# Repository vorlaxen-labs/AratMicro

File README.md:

# AratMicro

High-performance, open-source **micromouse** robot platform built for **[Robosam](https://robosam.org/)** and **MEB Robot** (Ministry of National Education Robotics Competition, Turkey).

AratMicro is a competition-focused maze-solving robot with a custom PCB, wall-detection sensors, dual-encoder drive, and STM32F411-based firmware. Hardware and software are developed together; all design files are shared in this repository.

## Competition target

This robot is designed to meet the maze-solving requirements of:

- **Robosam** — national robotics competition (micromouse / labyrinth category)
- **MEB Robot** — Ministry of National Education (MEB) robotics competition for schools

The mechanical dimensions, sensor layout, and control architecture are tuned for fast, reliable maze exploration and shortest-path solving under competition rules.

## Features

| Area | Detail |
|------|--------|
| **MCU** | STM32F411CEU6 — Cortex-M4 @ 100 MHz, 512 KB Flash, 128 KB RAM |
| **Motor driver** | DRV8833 — dual-channel H-bridge |
| **Wall sensors** | 4× IR receivers + 4× IR LEDs (front left/right, left, right) |
| **Maze solver** | Flood fill (16×16 grid) |
| **Position feedback** | Left/right quadrature encoders (L_ENC_A/B, R_ENC_A/B) |
| **I/O expansion** | PCF8574AP — I2C GPIO expander |
| **Power** | 2S LiPo → AP63203WU buck (3.3 V logic), separate motor rail |
| **Programming** | ST-Link SWD (PA13/PA14), optional UART Bluetooth |
| **Firmware** | PlatformIO + Arduino framework, C++17 |

## Mechanical (target parts)

| Part | Size | Notes |
|------|------|-------|
| **Motor** | 40 × 12 × 17 mm | 3 mm D-shaft |
| **Wheel** | 32 × 7 mm | 3 mm D-shaft |

> Mechanical CAD files are not yet included. Dimensions were chosen to match the PCB and drivetrain layout.

## Repository layout

```
AratMicro/
├── hardware/
│   └── pcb/          # KiCad 10 schematics and PCB (AratMicro.kicad_pro)
├── software/
│   ├── src/          # Firmware source code
│   ├── include/      # Public API headers
│   ├── lib/          # PlatformIO module libraries
│   ├── test/         # Host-side unit tests (Unity)
│   ├── docs/         # Architecture and hardware reference
│   └── platformio.ini
├── LICENSE
└── CONTRIBUTING.md
```

## Quick start

### Requirements

- [PlatformIO](https://platformio.org/) (VS Code extension or CLI)
- ST-Link V2 (or compatible programmer)
- KiCad 10.x (for hardware edits)

### Build and upload firmware

```bash
cd software
pio run -e aratmicro_f411
pio run -e aratmicro_f411 -t upload
```

### Host tests

Algorithms and core logic can be tested on the host:

```bash
cd software
pio test -e native
```

### Hardware

KiCad project: `hardware/pcb/AratMicro.kicad_pro`

Schematic sub-sheets:

| Sheet | File | Contents |
|-------|------|----------|
| Power Supply | `power_supply.kicad_sch` | 2S LiPo input, buck, protection |
| MCU | `mcu.kicad_sch` | STM32F411, clocks, SWD, I/O |
| Motor Controller | `mc.kicad_sch` | DRV8833 motor driver |
| Sensor Unit | `su.kicad_sch` | IR wall-detection circuit |

Full BOM and signal list: [`hardware/README.md`](hardware/README.md)

## Software architecture

Firmware is organized in layers:

- **core** — Hardware-independent application lifecycle
- **platform** — Time and pin abstractions
- **lib/** — Motor, IMU, maze solver modules (planned)

Details: [`software/docs/architecture.md`](software/docs/architecture.md)

## Status

| Component | Status |
|-----------|--------|
| PCB schematic | Active development |
| PCB layout | Active development |
| Firmware skeleton | Available |
| Motor driver code | Planned |
| Wall sensor code | Planned |
| Maze solver (flood fill) | Available (host-tested) |
| Mechanical CAD | Planned |

## Contributing

Contributions are welcome. Please read [`CONTRIBUTING.md`](CONTRIBUTING.md).

## License

This project is released under the [MIT License](LICENSE) — hardware and software may be used, modified, and shared freely.

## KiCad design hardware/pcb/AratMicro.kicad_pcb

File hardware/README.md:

# AratMicro — Hardware

KiCad 10 main board (PCB) design for the Robosam and MEB Robot micromouse platform. Project file: [`pcb/AratMicro.kicad_pro`](pcb/AratMicro.kicad_pro)

## Schematic hierarchy

```
AratMicro.kicad_sch
├── Power Supply/      power_supply.kicad_sch
├── MCU/               mcu.kicad_sch
├── Motor Controller Unit/   mc.kicad_sch
└── Sensor Unit/       su.kicad_sch
```

## Key components (BOM summary)

| Ref | Part | Description |
|-----|------|-------------|
| U2 | STM32F411CEU6 | Main MCU, UFQFPN-48 |
| U3 | DRV8833PWP | Dual H-bridge motor driver, HTSSOP-16 |
| U4 | PCF8574AP | I2C GPIO expander |
| U1 | AP63203WU | 2 A buck, fixed 3.3 V output |
| Y1 | 8 MHz crystal | HSE |
| Y2 | 32.768 kHz crystal | LSE (RTC) |
| BZ1 | Murata PKMCS0909E | Piezo buzzer |
| J (LiPo) | 2S LiPo connector | Battery input |

Protection: polyfuse, TVS diode, AO3401A P-channel MOSFET (power path).

## MCU signal map

Signal names are taken from schematic hierarchical labels. STM32 pin assignments will be finalized during PCB layout.

### Motor driver (DRV8833)

| Signal | Direction | Description |
|--------|-----------|-------------|
| MC_IN1 | MCU → DRV | Motor A direction 1 |
| MC_IN2 | MCU → DRV | Motor A direction 2 |
| MC_BIN1 | MCU → DRV | Motor B direction 1 |
| MC_BIN2 | MCU → DRV | Motor B direction 2 |
| MC_SLEEP | MCU → DRV | Sleep / enable |
| MC_FAULT | DRV → MCU | Fault output |
| AOUT1, AOUT2 | DRV → motor | Motor A |
| BOUT1, BOUT2 | DRV → motor | Motor B |

### Encoders

| Signal | Description |
|--------|-------------|
| L_ENC_A, L_ENC_B | Left wheel quadrature |
| R_ENC_A, R_ENC_B | Right wheel quadrature |

### Wall sensors (IR)

| Signal | Description |
|--------|-------------|
| IR_ON | Enable IR LEDs (Sensor Unit) |
| REC_F_L | Front-left receiver |
| REC_F_R | Front-right receiver |
| REC_L | Left wall receiver |
| REC_R | Right wall receiver |

The Sensor Unit uses 4× IR receivers paired with 4× IR LEDs (one emitter per direction: front-left, front-right, left, right). LED drivers are controlled via BC817 NPN transistors.

### Other

| Signal | Description |
|--------|-------------|
| SNIFF_SDA, SNIFF_SCL | I2C (IMU / external sensor bus) |
| BT_TX, BT_RX | UART — wireless module (optional) |
| Buzzer | Audio feedback |
| LED1–LED4 | Status LEDs |
| PA13, PA14 | SWD (ST-Link) |
| NRST, BOOT0 | Reset and boot mode |
| BATTS | Battery voltage (ADC) |

## Power architecture

```
2S LiPo (7.4 V nominal)
    │
    ├── Motor rail ──► DRV8833 VM
    │
    └── AP63203WU buck ──► +3.3 V logic
            │
            ├── STM32F411
            ├── PCF8574AP
            └── Sensor Unit (IR circuit)
```

Logic runs at 3.3 V; motor supply is driven directly from the battery rail. Polyfuse and TVS provide input protection.

## Mechanical interface

The drivetrain is designed for these off-the-shelf parts:

| Part | Size |
|------|------|
| DC motor | 40 × 12 × 17 mm, 3 mm D-shaft |
| Wheel | 32 × 7 mm, 3 mm D-shaft |

Motor connectors are defined on the Motor Controller Unit sheet.

## Opening in KiCad

1. Install KiCad 10.x.
2. Open `pcb/AratMicro.kicad_pro`.
3. Use the top-level hierarchy sheet in Eeschema to navigate sub-sheets.

## Fabrication

When PCB layout is complete:

- Export Gerber and drill files to `hardware/pcb/fabrication/`.
- BOM CSV: Eeschema → Tools → Generate Bill of Materials.

> **Note:** Layout and fabrication files are not final yet; the repository version is under active development.

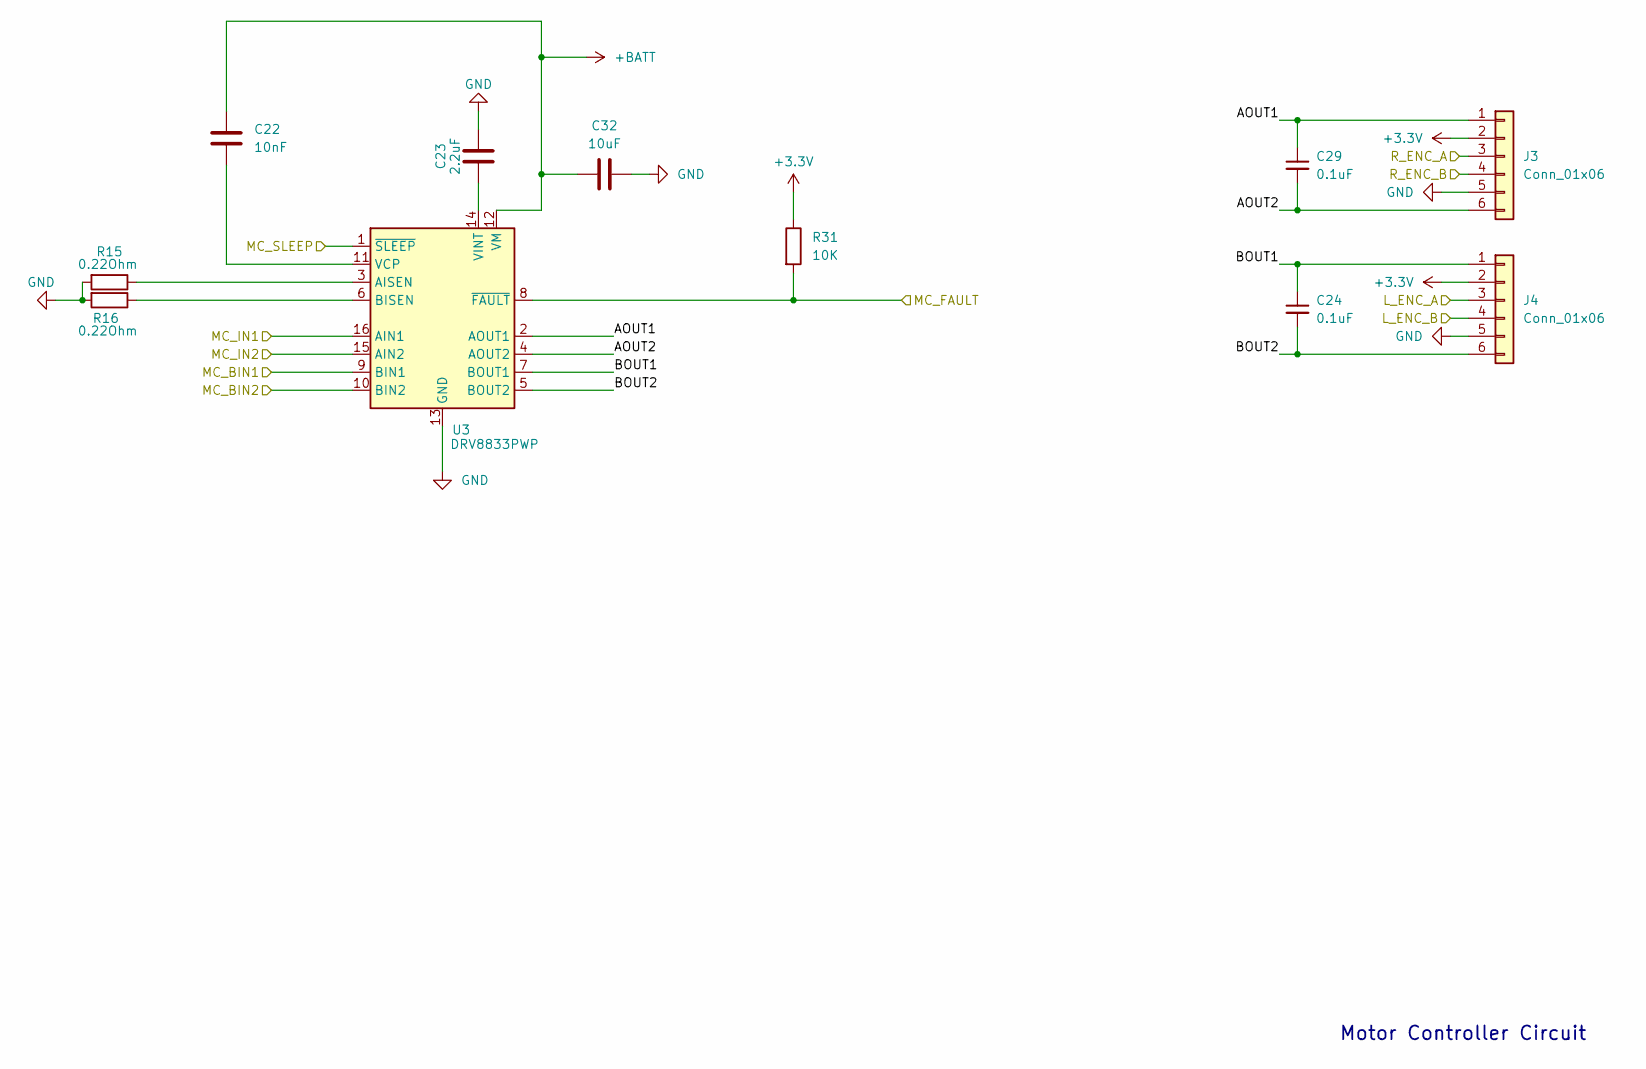
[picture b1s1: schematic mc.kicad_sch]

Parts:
C22: 10nF; C_0603_1608Metric
C23: 2.2uF; C_0603_1608Metric
C24, C29: 0.1uF; C_0603_1608Metric
C32: 10uF; C_0805_2012Metric
J3, J4: Conn_01x06; PinHeader_1x06_P2.54mm_Vertical
R15, R16: 0.22Ohm; R_0805_2012Metric
R31: 10K; R_0603_1608Metric
U3: DRV8833PWP; HTSSOP-16-1EP_4.4x5mm_P0.65mm_EP3.4x5mm_Mask2.46x2.31mm_The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

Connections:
+3.3V: J3.2, J4.2, R31.1; also elsewhere on the board
+BATT: C22.1, C32.1, U3.12 (VM); also elsewhere on the board
/Microcontroller Unit/L_ENC_A: J4.3; also elsewhere on the board
/Microcontroller Unit/L_ENC_B: J4.4; also elsewhere on the board
/Microcontroller Unit/MC_BIN1: U3.9 (BIN1); also elsewhere on the board
/Microcontroller Unit/MC_BIN2: U3.10 (BIN2); also elsewhere on the board
/Microcontroller Unit/MC_FAULT: R31.2, U3.8 (~FAULT); also elsewhere on the board
/Microcontroller Unit/MC_IN1: U3.16 (AIN1); also elsewhere on the board
/Microcontroller Unit/MC_IN2: U3.15 (AIN2); also elsewhere on the board
/Microcontroller Unit/MC_SLEEP: U3.1 (~SLEEP); also elsewhere on the board
/Microcontroller Unit/R_ENC_A: J3.3; also elsewhere on the board
/Microcontroller Unit/R_ENC_B: J3.4; also elsewhere on the board
/Motor Controller/AOUT1: C29.1, J3.1, U3.2 (AOUT1)
/Motor Controller/AOUT2: C29.2, J3.6, U3.4 (AOUT2)
/Motor Controller/BOUT1: C24.1, J4.1, U3.7 (BOUT1)
/Motor Controller/BOUT2: C24.2, J4.6, U3.5 (BOUT2)
GND: C23.2, C32.2, J3.5, J4.5, R15.2, R16.2, U3.13 (GND), U3.17 (GND); also elsewhere on the board
unnamed: R15.1, U3.3 (AISEN)
unnamed: R16.1, U3.6 (BISEN)
unnamed: C22.2, U3.11 (VCP)
unnamed: C23.1, U3.14 (VINT)

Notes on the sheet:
Motor Controller Circuit

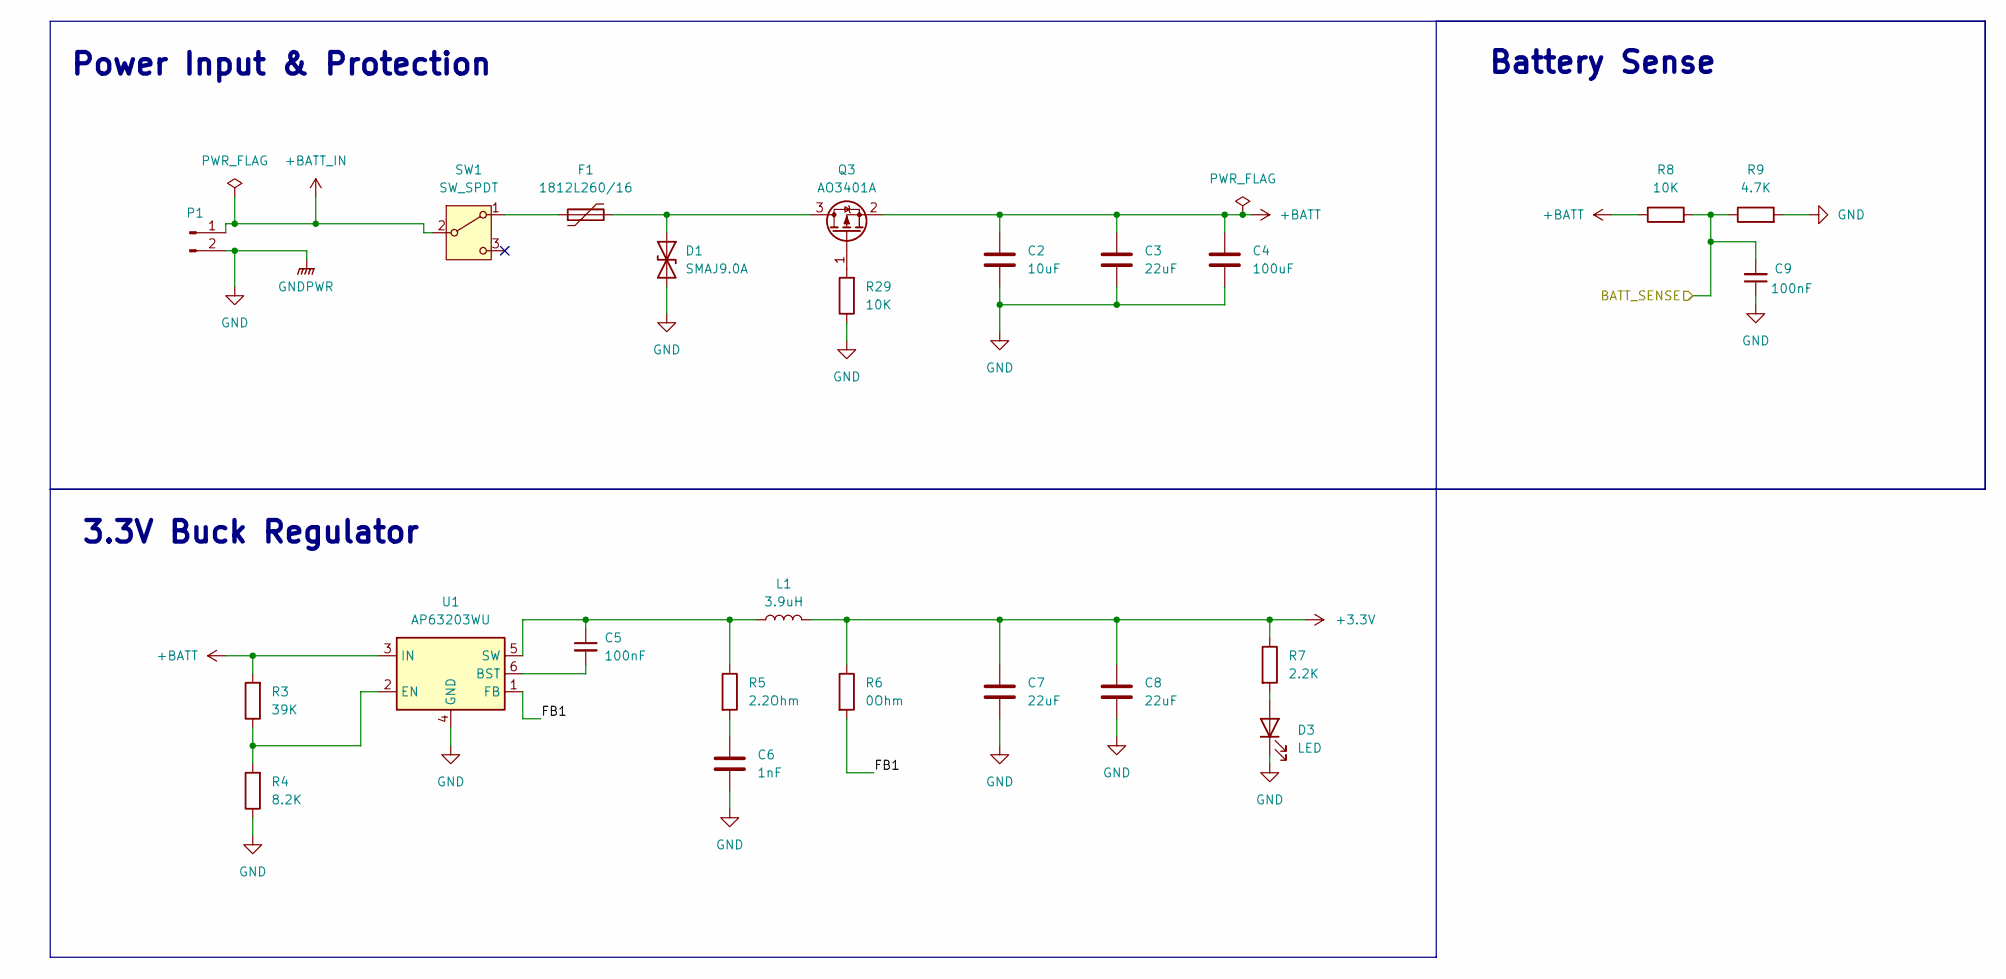
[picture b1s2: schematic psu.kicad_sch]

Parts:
C2: 10uF; C_0805_2012Metric
C3: 22uF; C_1206_3216Metric
C4: 100uF; C_1206_3216Metric
C5, C9: 100nF; C_0603_1608Metric
C6: 1nF; C_0603_1608Metric
C7: 22uF; C_0805_2012Metric_Pad1.18x1.45mm
C8: 22uF; C_0805_2012Metric
D1: SMAJ9.0A; D_SMA
D3: LED; LED_0603_1608Metric
F1: 1812L260/16; Fuse_1812_4532Metric
L1: 3.9uH; L_Sunlord_SWPA4030S
P1: 2S LiPo Connector; PinHeader_1x02_P2.54mm_Vertical
Q3: AO3401A; SOT-23
R3: 39K; R_0603_1608Metric
R4: 8.2K; R_0603_1608Metric
R5: 2.2Ohm; R_1206_3216Metric_Pad1.30x1.75mm_HandSolder
R6: 0Ohm; R_0603_1608Metric
R7: 2.2K; R_0603_1608Metric
R8, R29: 10K; R_0603_1608Metric
R9: 4.7K; R_0603_1608Metric
SW1: SW_SPDT; SW_SPDT_PCM12
U1: AP63203WU; TSOT-23-6

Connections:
+3.3V: C7.1, C8.1, L1.2, R6.1, R7.1; also elsewhere on the board
+BATT: C2.1, C3.1, C4.1, Q3.2 (S), R3.2, R8.1, U1.3 (IN); also elsewhere on the board
+BATT_IN: P1.1, SW1.2 (B)
/Microcontroller Unit/BATT_SENSE: C9.2, R8.2, R9.1; also elsewhere on the board
/Power Supply/FB1: R6.2, U1.1 (FB)
GND: C2.2, C3.2, C4.2, C6.2, C7.2, C8.2, C9.1, D1.2 (A2), D3.1 (K), P1.2, R4.1, R9.2, R29.1, U1.4 (GND); also elsewhere on the board
unnamed: C6.1, R5.2
unnamed: D1.1 (A1), F1.2, Q3.3 (D)
unnamed: D3.2 (A), R7.2
unnamed: Q3.1 (G), R29.2
unnamed: F1.1, SW1.1 (A)
unnamed: C5.2, U1.6 (BST)
unnamed: R3.1, R4.2, U1.2 (EN)
unnamed: C5.1, L1.1, R5.1, U1.5 (SW)

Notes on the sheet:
3.3V Buck Regulator
Battery Sense
Power Input & Protection

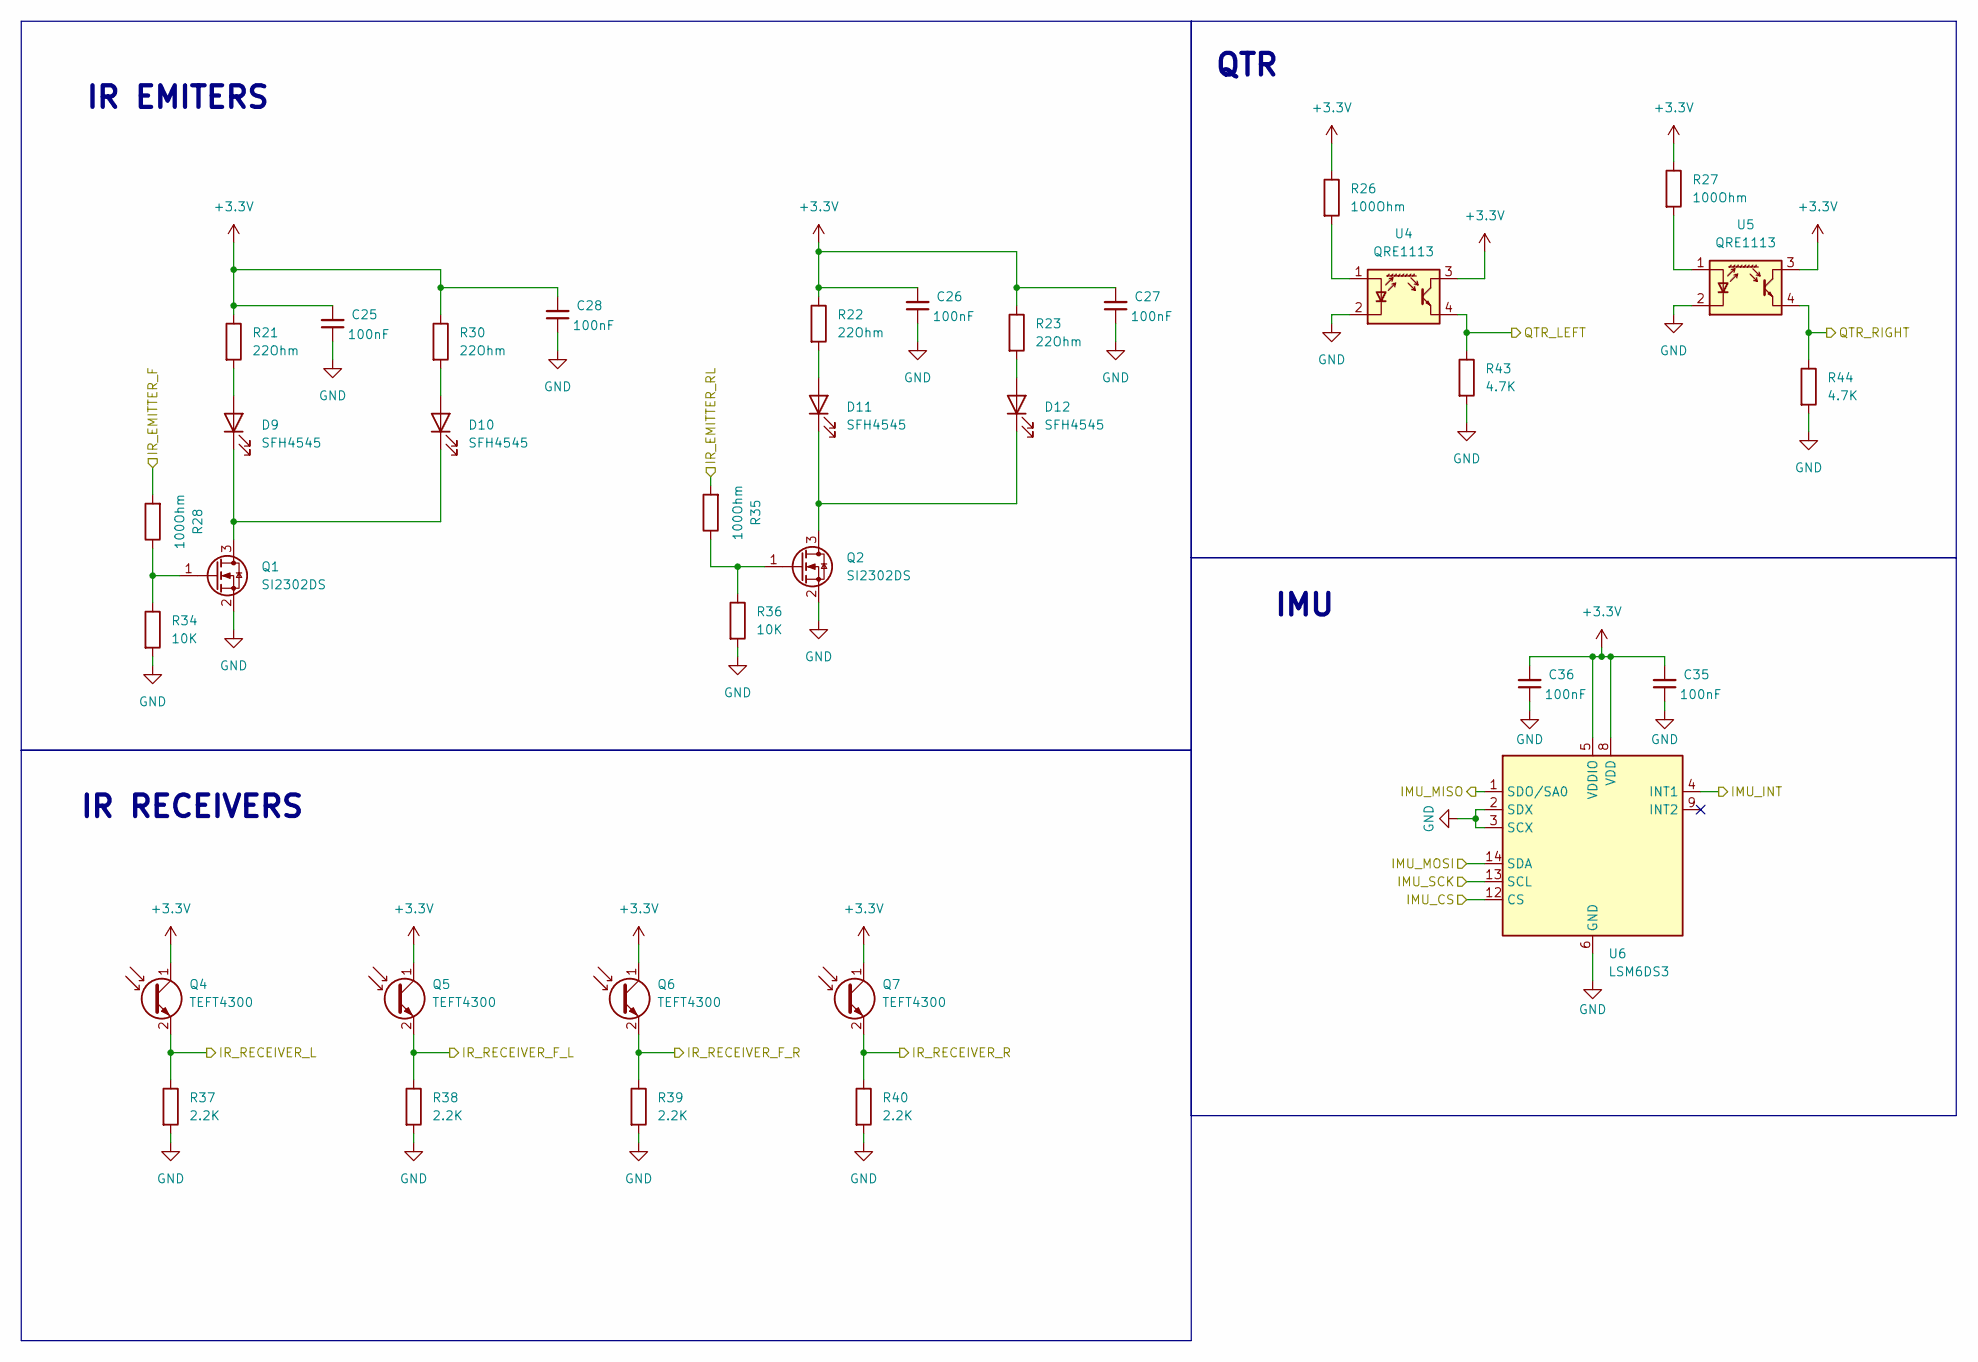
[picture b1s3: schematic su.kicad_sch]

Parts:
C25, C26, C27, C28, C35, C36: 100nF; C_0603_1608Metric
D9, D10, D11, D12: SFH4545; LED_D5.0mm_Horizontal_O1.27mm_Z15.0mm
Q1, Q2: SI2302DS; SOT-23
Q4, Q5, Q6, Q7: TEFT4300; LED_D3.0mm_IRBlack
R21, R22, R23, R30: 22Ohm; R_1206_3216Metric
R26, R27, R28, R35: 100Ohm; R_0603_1608Metric
R34, R36: 10K; R_0603_1608Metric
R37, R38, R39, R40: 2.2K; R_0603_1608Metric
R43, R44: 4.7K; R_0603_1608Metric
U4, U5: QRE1113; OnSemi_CASE100AQ
U6: LSM6DS3; LGA-14_3x2.5mm_P0.5mm_LayoutBorder3x4y

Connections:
+3.3V: C25.2, C26.2, C27.2, C28.2, C35.2, C36.2, Q4.1 (C), Q5.1 (C), Q6.1 (C), Q7.1 (C), R21.1, R22.1, R23.1, R26.1, R27.1, R30.1, U4.3, U5.3, U6.5 (VDDIO), U6.8 (VDD); also elsewhere on the board
/Microcontroller Unit/IMU_CS: U6.12 (CS); also elsewhere on the board
/Microcontroller Unit/IMU_INT: U6.4 (INT1); also elsewhere on the board
/Microcontroller Unit/IMU_MISO: U6.1 (SDO/SA0); also elsewhere on the board
/Microcontroller Unit/IMU_MOSI: U6.14 (SDA); also elsewhere on the board
/Microcontroller Unit/IMU_SCK: U6.13 (SCL); also elsewhere on the board
/Microcontroller Unit/IR_EMITTER_F: R28.2; also elsewhere on the board
/Microcontroller Unit/IR_EMITTER_RL: R35.2; also elsewhere on the board
/Microcontroller Unit/IR_RECEIVER_F_L: Q5.2 (E), R38.1; also elsewhere on the board
/Microcontroller Unit/IR_RECEIVER_F_R: Q6.2 (E), R39.1; also elsewhere on the board
/Microcontroller Unit/IR_RECEIVER_L: Q4.2 (E), R37.1; also elsewhere on the board
/Microcontroller Unit/IR_RECEIVER_R: Q7.2 (E), R40.1; also elsewhere on the board
/Microcontroller Unit/QTR_LEFT: R43.1, U4.4; also elsewhere on the board
/Microcontroller Unit/QTR_RIGHT: R44.1, U5.4; also elsewhere on the board
GND: C25.1, C26.1, C27.1, C28.1, C35.1, C36.1, Q1.2 (S), Q2.2 (S), R34.2, R36.2, R37.2, R38.2, R39.2, R40.2, R43.2, R44.2, U4.2 (K), U5.2 (K), U6.2 (SDX), U6.3 (SCX), U6.6 (GND), U6.7 (GND); also elsewhere on the board
unnamed: D9.2 (A), R21.2
unnamed: D10.2 (A), R30.2
unnamed: D9.1 (K), D10.1 (K), Q1.3 (D)
unnamed: D11.2 (A), R22.2
unnamed: D11.1 (K), D12.1 (K), Q2.3 (D)
unnamed: D12.2 (A), R23.2
unnamed: Q1.1 (G), R28.1, R34.1
unnamed: Q2.1 (G), R35.1, R36.1
unnamed: R26.2, U4.1 (A)
unnamed: R27.2, U5.1 (A)

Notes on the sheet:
IMU
IR EMITERS
QTR
IR RECEIVERS

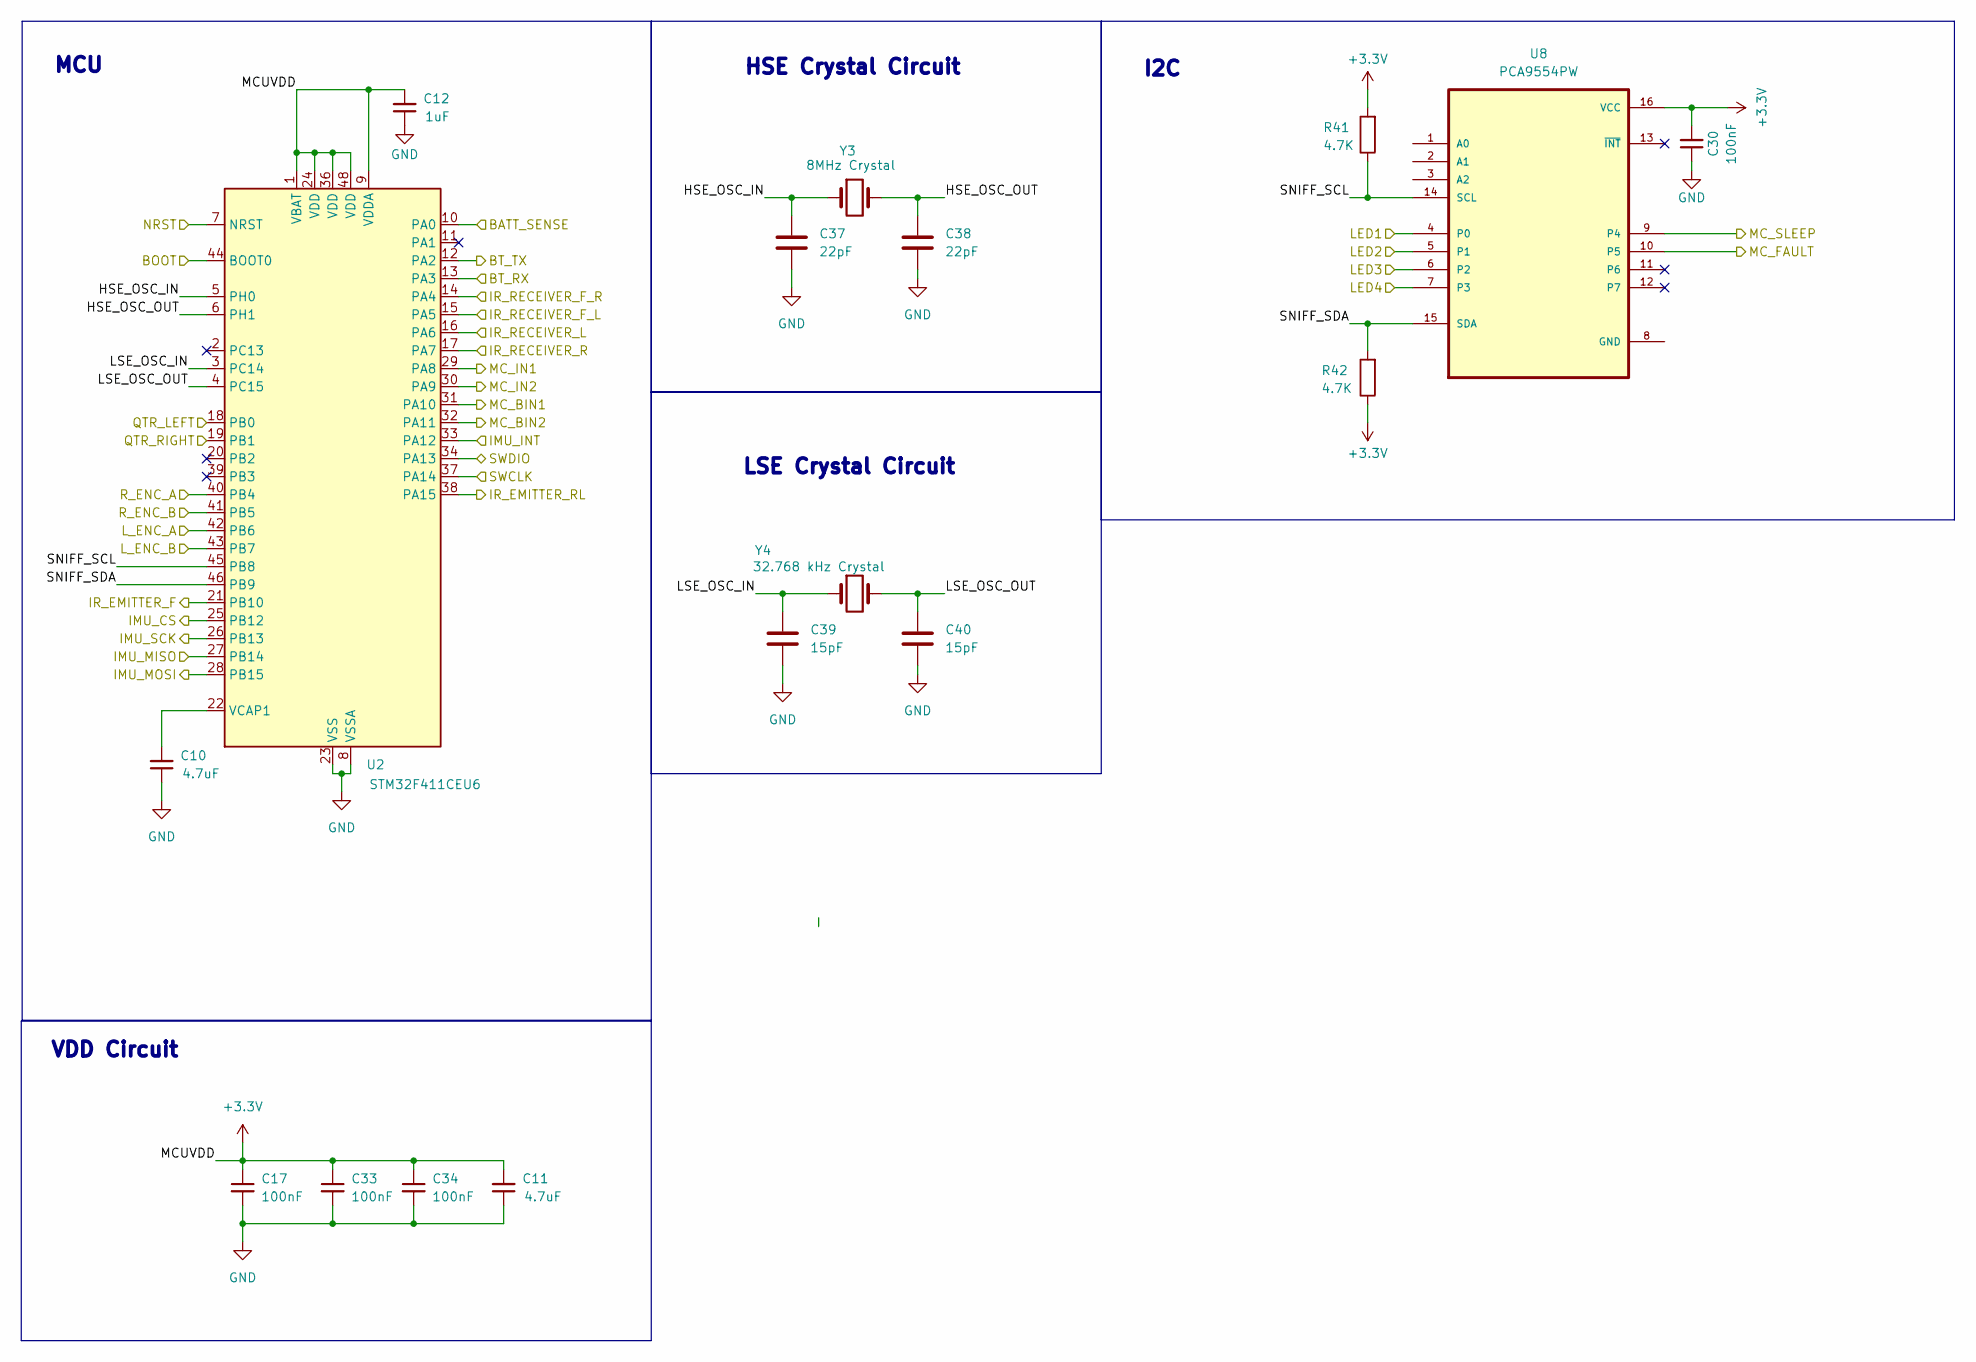
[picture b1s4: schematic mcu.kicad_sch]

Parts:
C10, C11: 4.7uF; C_0805_2012Metric
C12: 1uF; C_0603_1608Metric
C17, C30, C33, C34: 100nF; C_0603_1608Metric
C37, C38: 22pF; C_0603_1608Metric
C39, C40: 15pF; C_0603_1608Metric
R41, R42: 4.7K; R_0603_1608Metric
U2: STM32F411CEU6; QFN-48-1EP_7x7mm_P0.5mm_EP5.6x5.6mm
U8: PCA9554PW; SOP65P640X120-16N; DigiKey_Part_Number 2156-PCA9554PW-ND
Y3: 8MHz Crystal; Crystal_SMD_3225-4Pin_3.2x2.5mm_HandSoldering
Y4: 32.768 kHz Crystal; Crystal_SMD_3225-4Pin_3.2x2.5mm_HandSoldering

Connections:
+3.3V: C11.2, C12.2, C17.1, C30.2, C33.1, C34.1, R41.2, R42.1, U2.1 (VBAT), U2.9 (VDDA), U2.24 (VDD), U2.36 (VDD), U2.48 (VDD), U8.16 (VCC); also elsewhere on the board
/Microcontroller Unit/BATT_SENSE: U2.10 (PA0); also elsewhere on the board
/Microcontroller Unit/BOOT: U2.44 (BOOT0); also elsewhere on the board
/Microcontroller Unit/BT_RX: U2.13 (PA3); also elsewhere on the board
/Microcontroller Unit/BT_TX: U2.12 (PA2); also elsewhere on the board
/Microcontroller Unit/HSE_OSC_IN: C37.1, U2.5 (PH0), Y3.1
/Microcontroller Unit/HSE_OSC_OUT: C38.1, U2.6 (PH1), Y3.2
/Microcontroller Unit/IMU_CS: U2.25 (PB12); also elsewhere on the board
/Microcontroller Unit/IMU_INT: U2.33 (PA12); also elsewhere on the board
/Microcontroller Unit/IMU_MISO: U2.27 (PB14); also elsewhere on the board
/Microcontroller Unit/IMU_MOSI: U2.28 (PB15); also elsewhere on the board
/Microcontroller Unit/IMU_SCK: U2.26 (PB13); also elsewhere on the board
/Microcontroller Unit/IR_EMITTER_F: U2.21 (PB10); also elsewhere on the board
/Microcontroller Unit/IR_EMITTER_RL: U2.38 (PA15); also elsewhere on the board
/Microcontroller Unit/IR_RECEIVER_F_L: U2.15 (PA5); also elsewhere on the board
/Microcontroller Unit/IR_RECEIVER_F_R: U2.14 (PA4); also elsewhere on the board
/Microcontroller Unit/IR_RECEIVER_L: U2.16 (PA6); also elsewhere on the board
/Microcontroller Unit/IR_RECEIVER_R: U2.17 (PA7); also elsewhere on the board
/Microcontroller Unit/LED1: U8.4 (P0); also elsewhere on the board
/Microcontroller Unit/LED2: U8.5 (P1); also elsewhere on the board
/Microcontroller Unit/LED3: U8.6 (P2); also elsewhere on the board
/Microcontroller Unit/LED4: U8.7 (P3); also elsewhere on the board
/Microcontroller Unit/LSE_OSC_IN: C39.1, U2.3 (PC14), Y4.1
/Microcontroller Unit/LSE_OSC_OUT: C40.1, U2.4 (PC15), Y4.2
/Microcontroller Unit/L_ENC_A: U2.42 (PB6); also elsewhere on the board
/Microcontroller Unit/L_ENC_B: U2.43 (PB7); also elsewhere on the board
/Microcontroller Unit/MC_BIN1: U2.31 (PA10); also elsewhere on the board
/Microcontroller Unit/MC_BIN2: U2.32 (PA11); also elsewhere on the board
/Microcontroller Unit/MC_FAULT: U8.10 (P5); also elsewhere on the board
/Microcontroller Unit/MC_IN1: U2.29 (PA8); also elsewhere on the board
/Microcontroller Unit/MC_IN2: U2.30 (PA9); also elsewhere on the board
/Microcontroller Unit/MC_SLEEP: U8.9 (P4); also elsewhere on the board
/Microcontroller Unit/NRST: U2.7 (NRST); also elsewhere on the board
/Microcontroller Unit/QTR_LEFT: U2.18 (PB0); also elsewhere on the board
/Microcontroller Unit/QTR_RIGHT: U2.19 (PB1); also elsewhere on the board
/Microcontroller Unit/R_ENC_A: U2.40 (PB4); also elsewhere on the board
/Microcontroller Unit/R_ENC_B: U2.41 (PB5); also elsewhere on the board
/Microcontroller Unit/SNIFF_SCL: R41.1, U2.45 (PB8), U8.14 (SCL)
/Microcontroller Unit/SNIFF_SDA: R42.2, U2.46 (PB9), U8.15 (SDA)
/Microcontroller Unit/SWCLK: U2.37 (PA14); also elsewhere on the board
/Microcontroller Unit/SWDIO: U2.34 (PA13); also elsewhere on the board
GND: C10.1, C11.1, C12.1, C17.2, C30.1, C33.2, C34.2, C37.2, C38.2, C39.2, C40.2, U2.8 (VSSA), U2.23 (VSS), U2.35 (VSS), U2.47 (VSS), U2.49 (VSS); also elsewhere on the board
unnamed: C10.2, U2.22 (VCAP1)

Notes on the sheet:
VDD Circuit
HSE Crystal Circuit
MCU
I2C
LSE Crystal Circuit

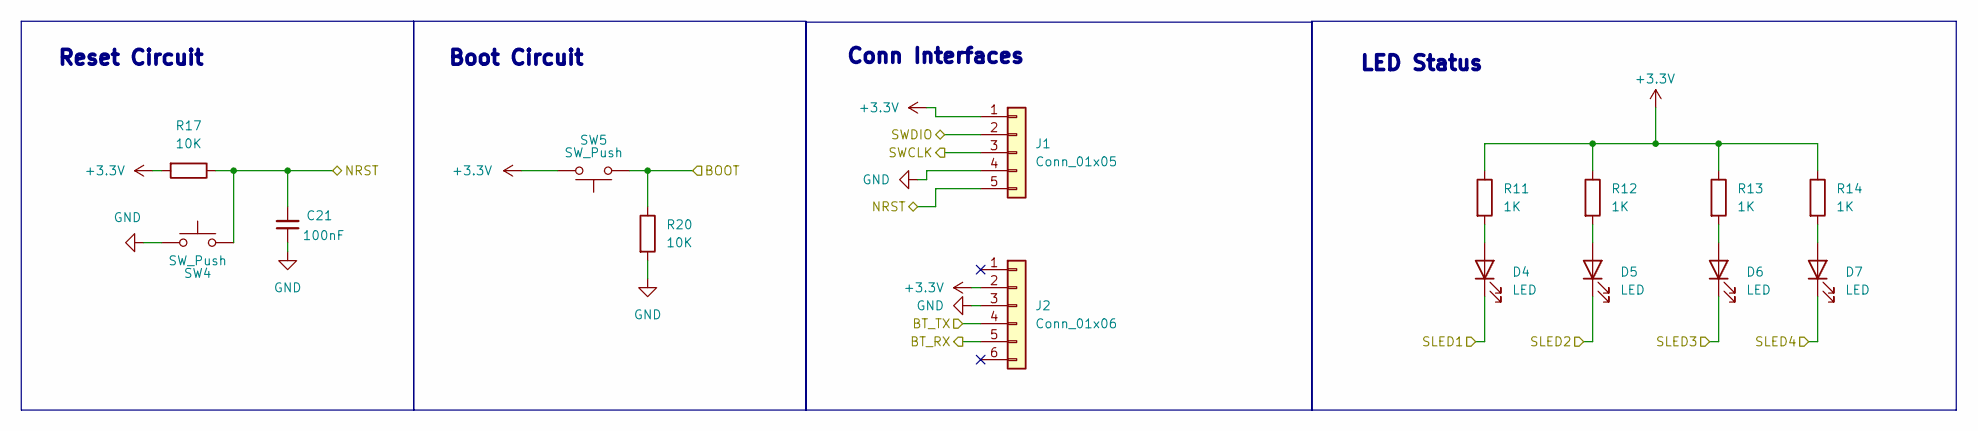
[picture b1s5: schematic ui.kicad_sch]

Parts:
C21: 100nF; C_0603_1608Metric
D4, D5, D6, D7: LED; LED_0603_1608Metric
J1: Conn_01x05; PinHeader_1x05_P1.00mm_Vertical
J2: Conn_01x06; PinHeader_1x06_P1.00mm_Vertical
R11, R12, R13, R14: 1K; R_0603_1608Metric
R17, R20: 10K; R_0603_1608Metric
SW4, SW5: SW_Push; SW_SPST_B3U-3000P

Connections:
+3.3V: J1.1, J2.2, R11.1, R12.1, R13.1, R14.1, R17.2, SW5.2; also elsewhere on the board
/Microcontroller Unit/BOOT: R20.1, SW5.1; also elsewhere on the board
/Microcontroller Unit/BT_RX: J2.5; also elsewhere on the board
/Microcontroller Unit/BT_TX: J2.4; also elsewhere on the board
/Microcontroller Unit/LED1: D4.1 (K); also elsewhere on the board
/Microcontroller Unit/LED2: D5.1 (K); also elsewhere on the board
/Microcontroller Unit/LED3: D6.1 (K); also elsewhere on the board
/Microcontroller Unit/LED4: D7.1 (K); also elsewhere on the board
/Microcontroller Unit/NRST: C21.2, J1.5, R17.1, SW4.2; also elsewhere on the board
/Microcontroller Unit/SWCLK: J1.3; also elsewhere on the board
/Microcontroller Unit/SWDIO: J1.2; also elsewhere on the board
GND: C21.1, J1.4, J2.3, R20.2, SW4.1; also elsewhere on the board
unnamed: D4.2 (A), R11.2
unnamed: D5.2 (A), R12.2
unnamed: D6.2 (A), R13.2
unnamed: D7.2 (A), R14.2

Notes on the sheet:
LED Status
Conn Interfaces
Reset Circuit
Boot Circuit

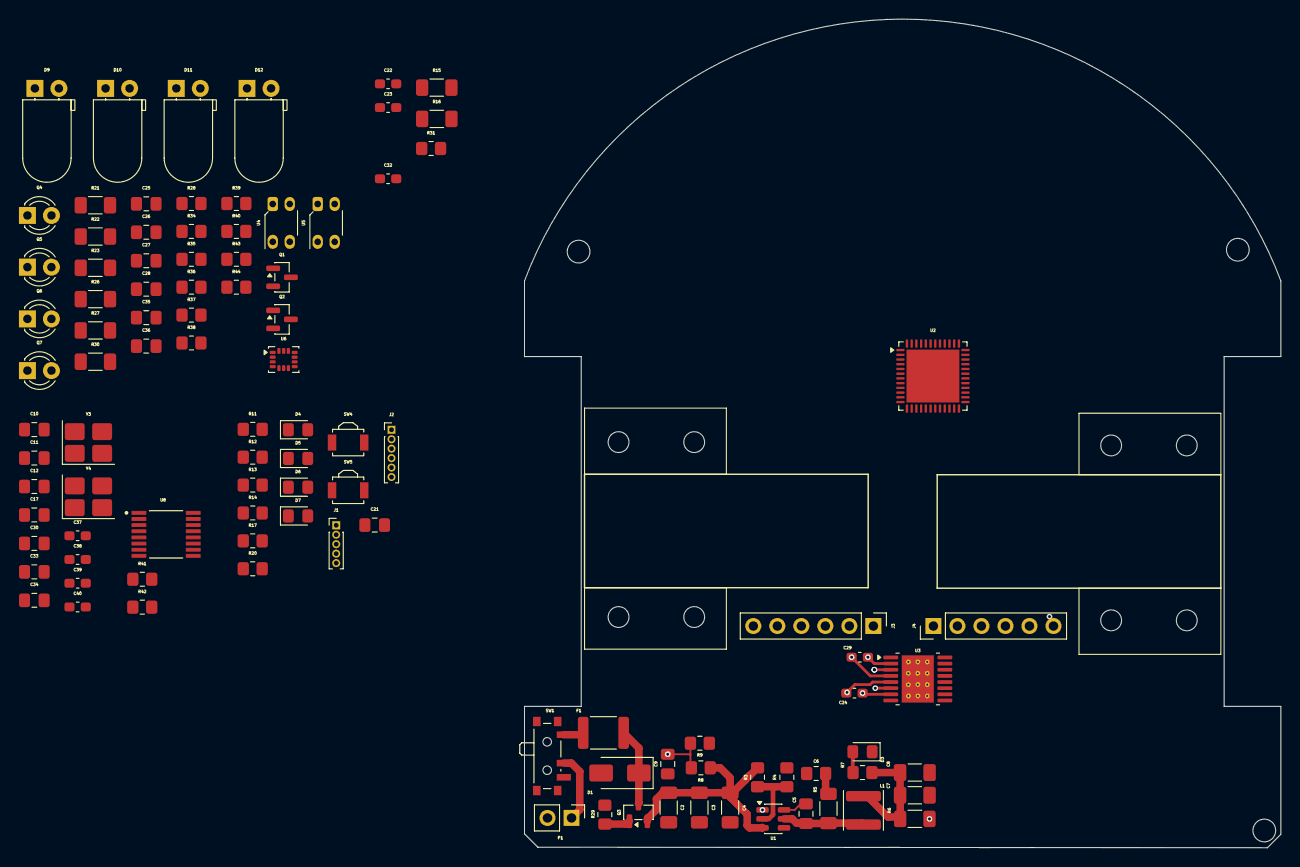
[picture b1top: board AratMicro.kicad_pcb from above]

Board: 4 copper layers, 80.0 x 87.6 mm, 102 parts (0 on the bottom side), 76 nets.
